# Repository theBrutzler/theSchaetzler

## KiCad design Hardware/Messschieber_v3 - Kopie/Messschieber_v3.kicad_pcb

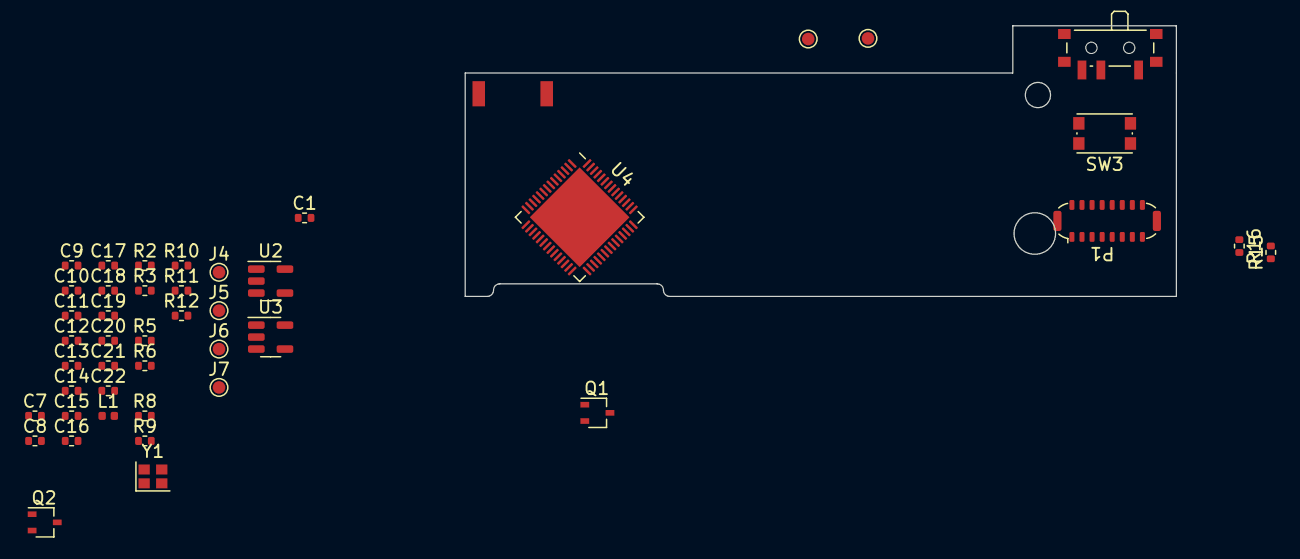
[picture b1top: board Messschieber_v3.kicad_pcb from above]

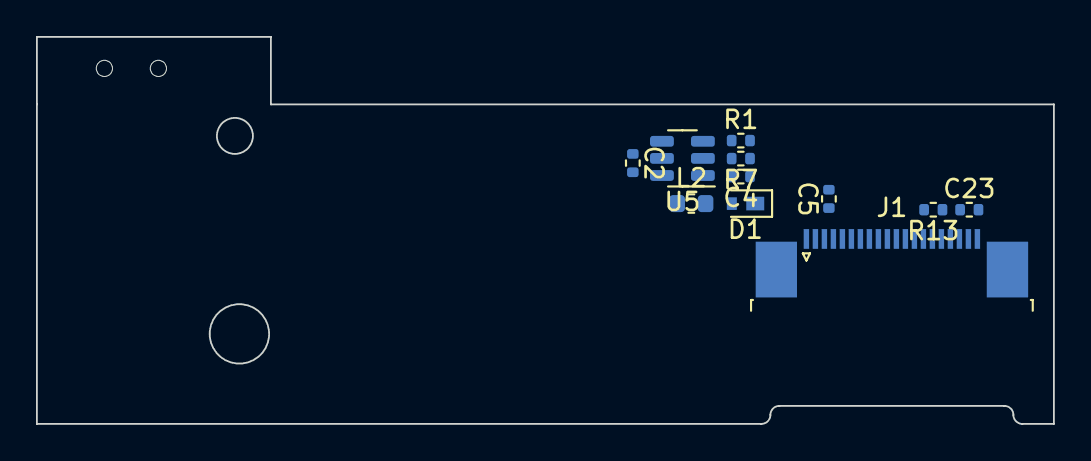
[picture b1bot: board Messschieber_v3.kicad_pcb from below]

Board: 2 copper layers, 56.5 x 21.5 mm, 56 parts (11 on the bottom side), 38 nets, no tracks yet.

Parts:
AE2: Antenna_Shield; RFANT5220110A2T
C1, C2, C4, C5, C10, C12, C14, C20, C21, C22, C23: 1µ; R_0402_1005Metric
C7, C11: 10µ; R_0402_1005Metric
C8, C9: 15p; R_0402_1005Metric
C13, C15, C16, C17, C18, C19: 100n; R_0402_1005Metric
D1: CDBVRL140; D_WBFBP
J1: SSD1357; TE_2-1734839-0_1x20-1MP_P0.5mm_Horizontal
J2, J3, J4, J5, J6, J7: Conn_01x01; TestPoint_Pad_D1.0mm
L1: 2n2; L_0402_1005Metric
L2: L; L_0603_1608Metric
P1: USB_C_Plug_USB2.0; USB_C_Plug_ShenzhenJingTuoJin_918-118A2021Y40002_Vertical
Q1, Q2: BC817W; SOT-323_SC-70
R1: 21K; R_0402_1005Metric
R2, R3: 22; R_0402_1005Metric
R5, R6, R7, R11, R12: 390K; R_0402_1005Metric
R8, R9, R10, R15, R16: 5K1; R_0402_1005Metric
R13: 1MEG; R_0402_1005Metric
SW1: SW_DIP_x01; SW_SPDT_PCM12
SW3: SW_Push; SW_Push_1P1T_NO_CK_KMR2
U2: AP7383-41W5-7 TPS70939DBVR; TSOT-23-5
U3: LN1134A332MR; TSOT-23-5
U4: ESP32-S3; QFN-56-1EP_7x7mm_P0.4mm_EP5.6x5.6mm
U5: MT3608; SOT-23-6
Y1: 40MHz; Crystal_SMD_2016-4Pin_2.0x1.6mm

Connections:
+3V3: C11.1, C12.2, C13.2, C17.2, C18.2, C19.2, C20.2, L1.1, R8.1, U3.5 (VOUT), U4.20 (VDD3P3_RTC), U4.46 (VDD3P3_CPU), U4.55 (VDDA), U4.56 (VDDA)
+12V: C4.1, D1.1 (K), J1.2, R7.1
/CS: J1.16, U4.18 (GPIO13/ADC2_CH2)
/D+: R2.1, U4.26 (GPIO20/USB_D+/ADC2_CH9)
/D-: R3.1, U4.25 (GPIO19/USB_D-/ADC2_CH8)
/DC: J1.14, U4.19 (GPIO14/ADC2_CH3)
/EN: C10.1, J1.15, R8.2, U4.4 (CHIP_PU/RESET), U5.4 (EN)
/GPIO9: R5.2, R6.1, U4.14 (GPIO9/ADC1_CH8)
/IO0: SW3.2, U4.5 (GPIO0/BOOT)
/IO2: Q2.3 (C), U4.7 (GPIO2/ADC1_CH1)
/IO4: Q1.3 (C), U4.9 (GPIO4/ADC1_CH3)
/SCL: J1.11, U4.17 (GPIO12/ADC2_CH1)
/SDA: J1.10, U4.16 (GPIO11/ADC2_CH0)
/VBAT: C2.1, C7.1, L2.1, R5.1, SW1.1, U2.5 (VOUT), U3.1 (VIN), U3.3 (EN), U5.5 (IN)
/VCC_DISPL: C23.1, J1.18, U4.23 (GPIO17/ADC2_CH6)
/VUSB: C1.2, P1.A4 (VBUS), P1.A9 (VBUS), P1.B4 (VBUS), P1.B9 (VBUS), U2.1 (VIN), U2.3 (EN)
GND: C1.1, C2.2, C4.2, C5.2, C7.2, C8.2, C9.2, C10.2, C11.2, C12.1, C13.1, C14.1, C15.1, C16.1, C17.1, C18.1, C19.1, C20.1, C21.2, C22.2, C23.2, J1.19, J3.1, J6.1, P1.A1 (GND), P1.A12 (GND), P1.B1 (GND), P1.B12 (GND), P1.S1 (SHIELD), Q1.2 (E), Q2.2 (E), R1.2, R6.2, R13.2, R15.2, R16.1, SW3.1, U2.2 (GND), U3.2 (GND), U4.57 (GND), U5.2 (GND), Y1.2, Y1.4
unnamed: AE2.1 (A), U4.1 (LNA_IN/RF)
unnamed: C21.1, R9.2, R10.1
unnamed: D1.2 (A), L2.2, U5.1 (SW)
unnamed: C5.1, J1.3
unnamed: J1.17, R13.1
unnamed: J2.1, SW1.2
unnamed: J4.1, R11.1
unnamed: J5.1, R12.1
unnamed: C22.1, J7.1, R10.2, U4.15 (GPIO10/ADC1_CH9)
unnamed: P1.A5 (CC), R15.1
unnamed: P1.A6 (D+), R2.2
unnamed: P1.A7 (D-), R3.2
unnamed: P1.B5 (VCONN), R16.2
unnamed: Q1.1 (B), R12.2
unnamed: Q2.1 (B), R11.2
unnamed: R9.1, U4.27 (GPIO21)
unnamed: C14.2, C15.2, U4.29 (VDD_SPI)
unnamed: C8.1, U4.53 (XTAL_N), Y1.3
unnamed: C9.1, U4.54 (XTAL_P), Y1.1
unnamed: R1.1, R7.2, U5.3 (FB)
VDD3P3: C16.2, L1.2, U4.2 (VDD3P3), U4.3 (VDD3P3)

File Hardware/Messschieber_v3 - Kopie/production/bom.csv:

Designator,Footprint,Quantity,Value,LCSC Part #
AE1,Texas_SWRA117D_2.4GHz_Left,1,Antenna_Shield,nc
"C1, C11, C2, C3, C7",0402,5,10µ,C315248
"C10, C12, C14, C20, C21, C22, C4, C5, C6",0402,9,1µ,C307413
"C13, C15, C16, C17, C18, C19",0402,6,100n,C1581
"C8, C9",0402,2,15p,C1548
D1,LED_Cree-PLCC4_2x2mm_CCW,1,WS2812B_Geaendertes_Symbol,C965555
J1,10118194,1,USB_B_Micro,C2926988
"J2, J3, J4, J5, J6, J7",TestPoint_Pad_D1.0mm,6,Conn_01x01,nc
L1,0402,1,2n2,C27122
"Q1, Q2",SOT-323_SC-70,2,BC817W,C75566
"R1, R11, R12, R4, R5, R6",0402,6,390K,C2906936
"R10, R13, R14, R8, R9",0402,5,5K1,C25905
"R2, R3, R7",0402,3,22,C2906914
SW1,SW_SPDT_PCM12,1,SW_DIP_x01,C223846
"SW2, SW3",microswitch,2,SW_Push,C913791
U1,SSD1306_OLED-0.91-128x32,1,SSD1306,nc
U2,TSOT-23-5,1,AP7383-41W5-7 TPS70939DBVR,C2868697
U3,TSOT-23-5,1,LN1134A332MR,C141419
U4,QFN-56-1EP_7x7mm_P0.4mm_EP5.6x5.6mm,1,ESP32-S3,C3013940
Y1,Crystal_SMD_2016-4Pin_2.0x1.6mm,1,40MHz,C424431

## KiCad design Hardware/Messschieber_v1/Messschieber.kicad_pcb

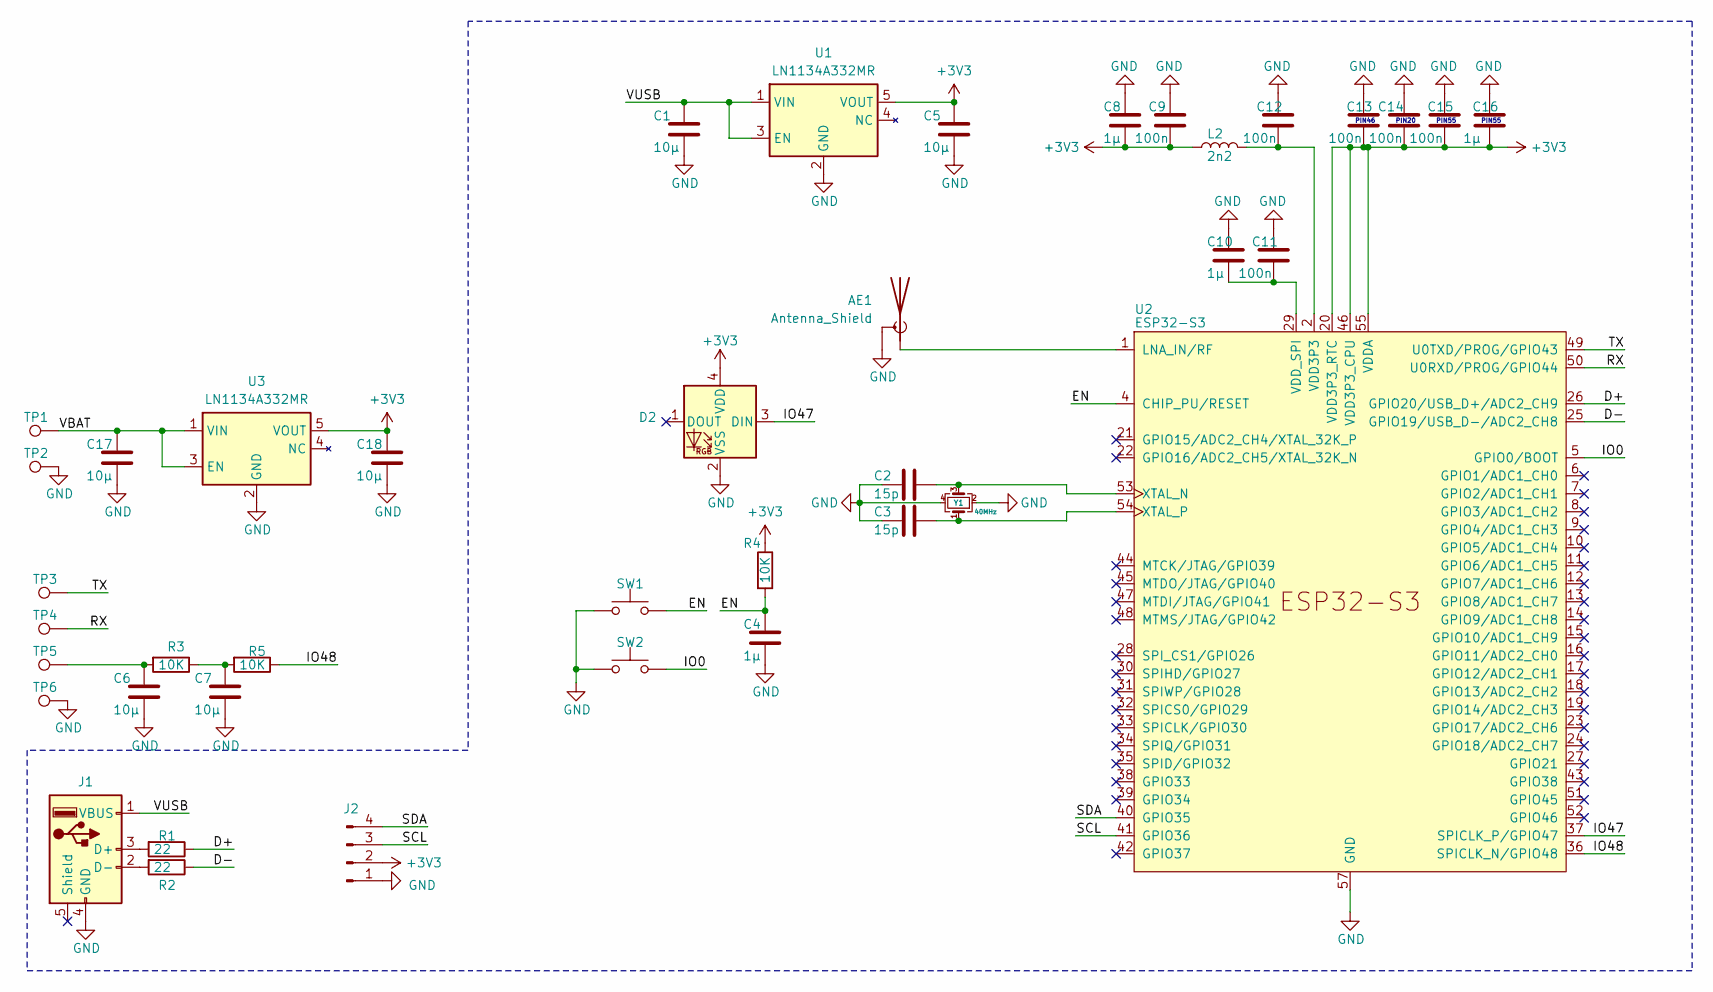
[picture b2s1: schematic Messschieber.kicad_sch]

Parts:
AE1: Antenna_Shield; Texas_SWRA117D_2.4GHz_Right
C1, C5, C6, C7, C17, C18: 10µ; R_0402_1005Metric
C2, C3: 15p; R_0402_1005Metric
C4, C8, C10, C16: 1µ; R_0402_1005Metric
C9, C11, C12, C13, C14, C15: 100n; R_0402_1005Metric
D2: WS2812B_Geaendertes_Symbol; LED_Cree-PLCC4_2x2mm_CCW; LCSC C965556
J1: USB_A; usb-PCB
J2: Conn_01x04_Pin; PinHeader_1x04_P2.54mm_Vertical
L2: 2n2; L_0402_1005Metric; LCSC C2941466
R1, R2: 22; R_0402_1005Metric
R3, R4, R5: 10K; R_0402_1005Metric
SW1: SW_Push; microswitch; LCSC C482003
SW2: SW_Push; microswitch; LCSC C100056
TP1, TP2, TP3, TP4, TP5, TP6: TestPoint; TestPoint_Pad_D1.5mm
U1, U3: LN1134A332MR; TSOT-23-5
U2: ESP32-S3; QFN-56-1EP_7x7mm_P0.4mm_EP5.6x5.6mm
Y1: 40MHz; Crystal_SMD_2016-4Pin_2.0x1.6mm; LCSC C424431

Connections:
+3V3: C5.1, C8.2, C9.2, C13.2, C14.2, C15.2, C16.2, C18.1, D2.4 (VDD), J2.2, L2.1, R4.1, U1.5 (VOUT), U2.20 (VDD3P3_RTC), U2.46 (VDD3P3_CPU), U2.55 (VDDA), U2.56 (VDDA), U3.5 (VOUT)
/D+: R1.1, U2.26 (GPIO20/USB_D+/ADC2_CH9)
/D-: R2.1, U2.25 (GPIO19/USB_D-/ADC2_CH8)
/EN: C4.1, R4.2, SW1.2, U2.4 (CHIP_PU/RESET)
/IO0: SW2.2, U2.5 (GPIO0/BOOT)
/IO47: D2.3 (DIN), U2.37 (SPICLK_P/GPIO47)
/IO48: R5.1, U2.36 (SPICLK_N/GPIO48)
/RX: TP4.1, U2.50 (U0RXD/PROG/GPIO44)
/SCL: J2.3, U2.41 (GPIO36)
/SDA: J2.4, U2.40 (GPIO35)
/TX: TP3.1, U2.49 (U0TXD/PROG/GPIO43)
/VBAT: C17.1, TP1.1, U3.1 (VIN), U3.3 (EN)
/VUSB: C1.1, J1.1 (VBUS), U1.1 (VIN), U1.3 (EN)
GND: AE1.2 (Shield), C1.2, C2.2, C3.2, C4.2, C5.2, C6.2, C7.2, C8.1, C9.1, C10.1, C11.1, C12.1, C13.1, C14.1, C15.1, C16.1, C17.2, C18.2, D2.2 (VSS), J1.4 (GND), J2.1, SW1.1, SW2.1, TP2.1, TP6.1, U1.2 (GND), U2.57 (GND), U3.2 (GND), Y1.2, Y1.4
unnamed: AE1.1 (A), U2.1 (LNA_IN/RF)
unnamed: C6.1, R3.2, TP5.1
unnamed: C7.1, R3.1, R5.2
unnamed: J1.3 (D+), R1.2
unnamed: J1.2 (D-), R2.2
unnamed: C10.2, C11.2, U2.29 (VDD_SPI)
unnamed: C2.1, U2.53 (XTAL_N), Y1.3
unnamed: C3.1, U2.54 (XTAL_P), Y1.1
VDD3P3: C12.2, L2.2, U2.2 (VDD3P3), U2.3 (VDD3P3)

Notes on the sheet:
PIN55
PIN20
PIN46

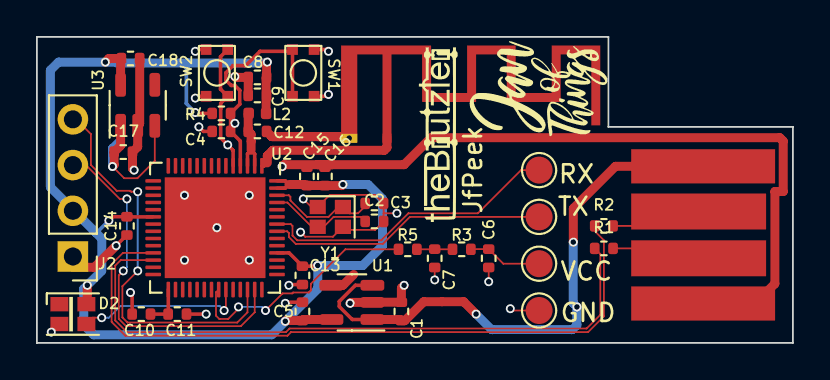
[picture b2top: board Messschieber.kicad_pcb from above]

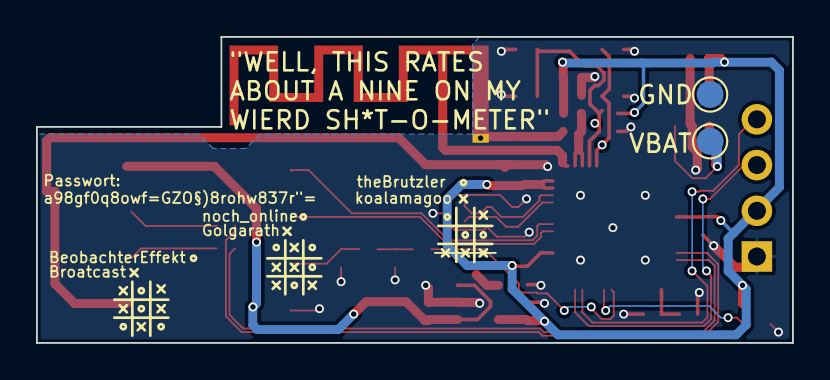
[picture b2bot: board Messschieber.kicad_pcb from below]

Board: 2 copper layers, 42.0 x 17.0 mm, 40 parts (2 on the bottom side), 23 nets.

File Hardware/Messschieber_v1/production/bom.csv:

Designator,Footprint,Quantity,Value,LCSC Part #
AE1,Texas_SWRA117D_2.4GHz_Right,1,Antenna_Shield,
"C1, C17, C18, C5, C6, C7",0402,6,10µ,
"C10, C16, C4, C8",0402,4,1µ,
"C11, C12, C13, C14, C15, C9",0402,6,100n,
"C2, C3",0402,2,15p,
D2,LED_Cree-PLCC4_2x2mm_CCW,1,WS2812B_Geaendertes_Symbol,C965556
J1,usb-PCB,1,USB_A,
J2,PinHeader_1x04_P2.54mm_Vertical,1,Conn_01x04_Pin,
L2,0402,1,2n2,C2941466
"R1, R2",0402,2,22,
"R3, R4, R5",0402,3,10K,
"SW1, SW2",microswitch,2,SW_Push,C482003
"TP1, TP2, TP3, TP4, TP5, TP6",TestPoint_Pad_D1.5mm,6,TestPoint,
"U1, U3",TSOT-23-5,2,LN1134A332MR,
U2,QFN-56-1EP_7x7mm_P0.4mm_EP5.6x5.6mm,1,ESP32-S3,
Y1,Crystal_SMD_2016-4Pin_2.0x1.6mm,1,40MHz,C424431

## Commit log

2024-01-17 schaematic board png
2024-02-08 BLE Upload
